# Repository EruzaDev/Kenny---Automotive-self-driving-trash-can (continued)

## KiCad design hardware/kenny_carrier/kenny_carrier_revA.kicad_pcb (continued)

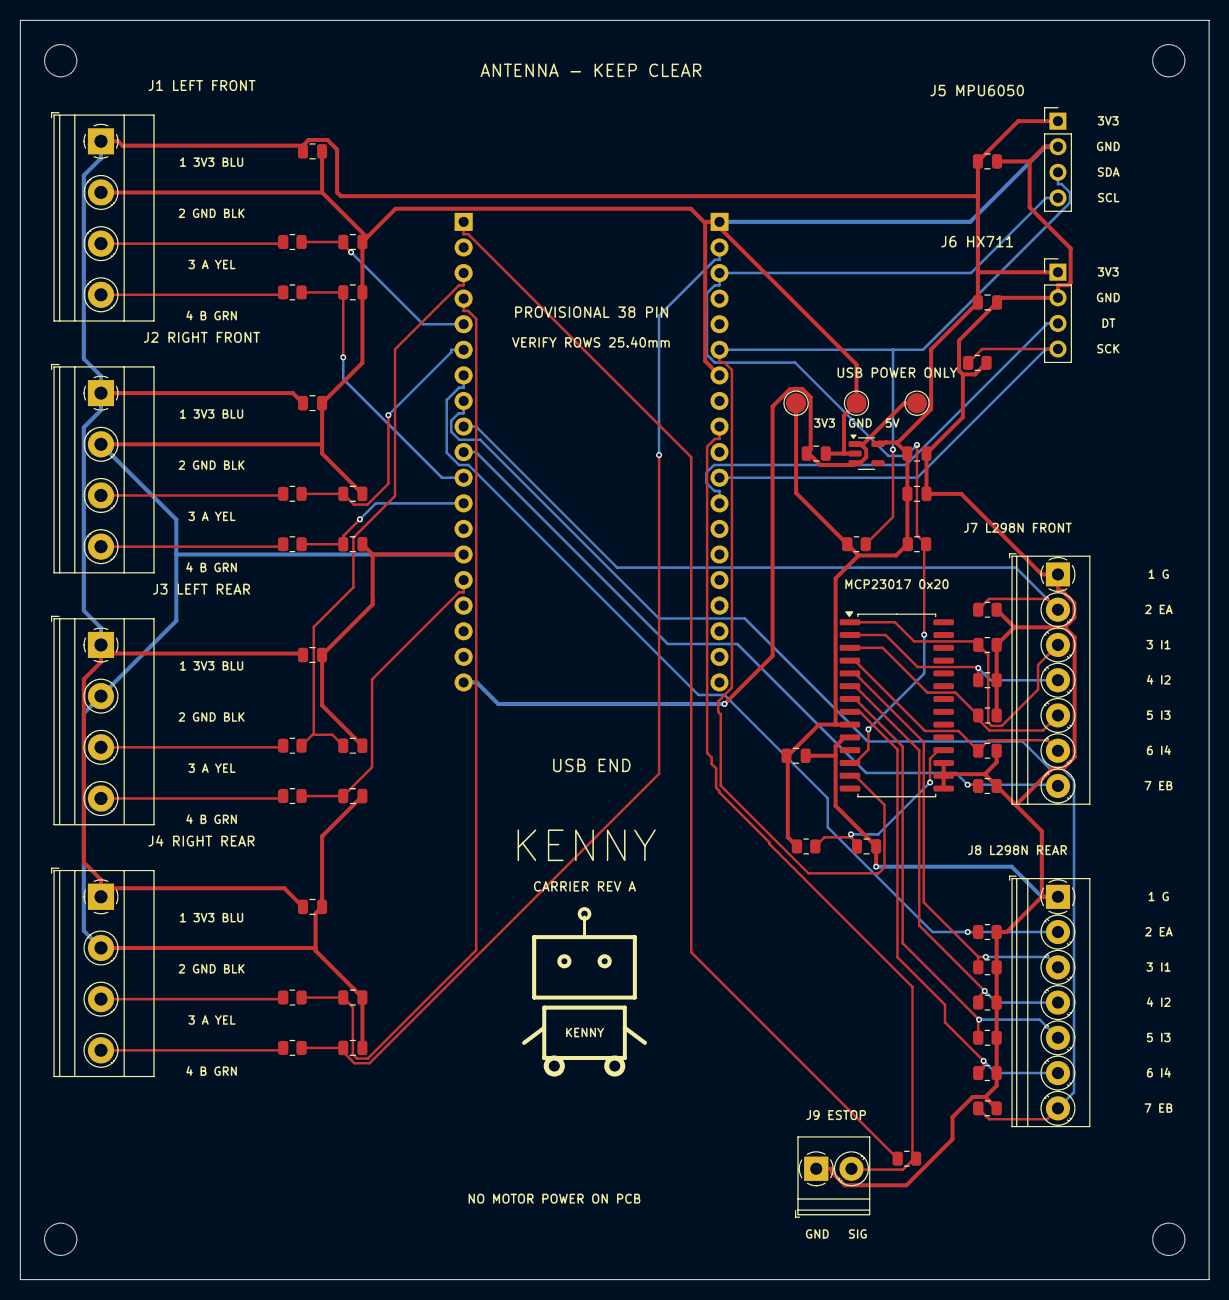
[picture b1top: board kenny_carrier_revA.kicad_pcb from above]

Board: 2 copper layers, 118.0 x 125.0 mm, 63 parts (0 on the bottom side), 38 nets.

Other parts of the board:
H1, H2, H3, H4: MountingHole_3.2mm_M3

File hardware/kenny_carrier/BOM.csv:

Reference,Value,Footprint,Description
U1,ESP32-WROOM 38pin PROVISIONAL,Kenny:ESP32_38_PROVISIONAL,2x19 female sockets; 2.54mm pitch; assumed 25.40mm row spacing; verify module
U2,MCP23017-E/SO,Package_SO:SOIC-28W_7.5x17.9mm_P1.27mm,"I2C address 0x20, GPB0..7 independent motor directions"
U3,AP2112K-3.3TRG1,Package_TO_SOT_SMD:SOT-23-5,Peripheral 3.3V LDO; input from DevKit USB 5V pin ONLY; 150mA initial budget
J1,LF ENCODER,"TerminalBlock_Phoenix:TerminalBlock_Phoenix_MKDS-1,5-4-5.08_1x04_P5.08mm_Horizontal","5.08mm 4-way terminal; 1 BLUE +3V3, 2 BLACK GND, 3 YELLOW A, 4 GREEN B"
R1,1k,Resistor_SMD:R_0805_2012Metric,"Encoder series resistor, together with 1nF gives 1us RC; NOT a level shifter"
C1,1nF 50V C0G,Capacitor_SMD:C_0805_2012Metric,
R2,1k,Resistor_SMD:R_0805_2012Metric,"Encoder series resistor, together with 1nF gives 1us RC; NOT a level shifter"
C2,1nF 50V C0G,Capacitor_SMD:C_0805_2012Metric,
C9,100nF 16V X7R,Capacitor_SMD:C_0805_2012Metric,
J2,RF ENCODER,"TerminalBlock_Phoenix:TerminalBlock_Phoenix_MKDS-1,5-4-5.08_1x04_P5.08mm_Horizontal","5.08mm 4-way terminal; 1 BLUE +3V3, 2 BLACK GND, 3 YELLOW A, 4 GREEN B"
R3,1k,Resistor_SMD:R_0805_2012Metric,"Encoder series resistor, together with 1nF gives 1us RC; NOT a level shifter"
C3,1nF 50V C0G,Capacitor_SMD:C_0805_2012Metric,
R4,1k,Resistor_SMD:R_0805_2012Metric,"Encoder series resistor, together with 1nF gives 1us RC; NOT a level shifter"
C4,1nF 50V C0G,Capacitor_SMD:C_0805_2012Metric,
C10,100nF 16V X7R,Capacitor_SMD:C_0805_2012Metric,
J3,LR ENCODER,"TerminalBlock_Phoenix:TerminalBlock_Phoenix_MKDS-1,5-4-5.08_1x04_P5.08mm_Horizontal","5.08mm 4-way terminal; 1 BLUE +3V3, 2 BLACK GND, 3 YELLOW A, 4 GREEN B"
R5,1k,Resistor_SMD:R_0805_2012Metric,"Encoder series resistor, together with 1nF gives 1us RC; NOT a level shifter"
C5,1nF 50V C0G,Capacitor_SMD:C_0805_2012Metric,
R6,1k,Resistor_SMD:R_0805_2012Metric,"Encoder series resistor, together with 1nF gives 1us RC; NOT a level shifter"
C6,1nF 50V C0G,Capacitor_SMD:C_0805_2012Metric,
C11,100nF 16V X7R,Capacitor_SMD:C_0805_2012Metric,
J4,RR ENCODER,"TerminalBlock_Phoenix:TerminalBlock_Phoenix_MKDS-1,5-4-5.08_1x04_P5.08mm_Horizontal","5.08mm 4-way terminal; 1 BLUE +3V3, 2 BLACK GND, 3 YELLOW A, 4 GREEN B"
R7,1k,Resistor_SMD:R_0805_2012Metric,"Encoder series resistor, together with 1nF gives 1us RC; NOT a level shifter"
C7,1nF 50V C0G,Capacitor_SMD:C_0805_2012Metric,
R8,1k,Resistor_SMD:R_0805_2012Metric,"Encoder series resistor, together with 1nF gives 1us RC; NOT a level shifter"
C8,1nF 50V C0G,Capacitor_SMD:C_0805_2012Metric,
C12,100nF 16V X7R,Capacitor_SMD:C_0805_2012Metric,
J5,MPU6050,Connector_PinHeader_2.54mm:PinHeader_1x04_P2.54mm_Vertical,"2.54mm Dupont: 3V3 GND SDA SCL; wire by signal, module header order can differ"
J6,HX711 MODULE,Connector_PinHeader_2.54mm:PinHeader_1x04_P2.54mm_Vertical,2.54mm Dupont: 3V3 GND DT SCK; raw load cell goes to HX711 E+/E-/A+/A-
J7,L298N FRONT,"TerminalBlock_Phoenix:TerminalBlock_Phoenix_PT-1,5-7-3.5-H_1x07_P3.50mm_Horizontal",3.50mm 7-way terminal: GND ENA IN1 IN2 IN3 IN4 ENB; logic only
J8,L298N REAR,"TerminalBlock_Phoenix:TerminalBlock_Phoenix_PT-1,5-7-3.5-H_1x07_P3.50mm_Horizontal",3.50mm 7-way terminal: GND ENA IN1 IN2 IN3 IN4 ENB; logic only
J9,ESTOP NC,"TerminalBlock_Phoenix:TerminalBlock_Phoenix_PT-1,5-2-3.5-H_1x02_P3.50mm_Horizontal",3.50mm 2-way terminal; normally-closed contact to GND; open=stop; external power cut remains required
R9,10k,Resistor_SMD:R_0805_2012Metric,Direction pull-down; MCP pins are high impedance during reset
R10,10k,Resistor_SMD:R_0805_2012Metric,Direction pull-down; MCP pins are high impedance during reset
R11,10k,Resistor_SMD:R_0805_2012Metric,Direction pull-down; MCP pins are high impedance during reset
R12,10k,Resistor_SMD:R_0805_2012Metric,Direction pull-down; MCP pins are high impedance during reset
R13,10k,Resistor_SMD:R_0805_2012Metric,Direction pull-down; MCP pins are high impedance during reset
R14,10k,Resistor_SMD:R_0805_2012Metric,Direction pull-down; MCP pins are high impedance during reset
R15,10k,Resistor_SMD:R_0805_2012Metric,Direction pull-down; MCP pins are high impedance during reset
R16,10k,Resistor_SMD:R_0805_2012Metric,Direction pull-down; MCP pins are high impedance during reset
R17,10k,Resistor_SMD:R_0805_2012Metric,Enable pull-down; REMOVE L298N ENA/ENB jumpers
R18,10k,Resistor_SMD:R_0805_2012Metric,Enable pull-down; REMOVE L298N ENA/ENB jumpers
R19,10k,Resistor_SMD:R_0805_2012Metric,Enable pull-down; REMOVE L298N ENA/ENB jumpers
R20,10k,Resistor_SMD:R_0805_2012Metric,Enable pull-down; REMOVE L298N ENA/ENB jumpers
R21,4.7k,Resistor_SMD:R_0805_2012Metric,I2C pull-up; depopulate if module pull-ups make total too low
R22,4.7k,Resistor_SMD:R_0805_2012Metric,I2C pull-up
R23,10k,Resistor_SMD:R_0805_2012Metric,MCP reset pull-up
R24,10k,Resistor_SMD:R_0805_2012Metric,E-stop input pull-up
R25,10k,Resistor_SMD:R_0805_2012Metric,Hold HX711 clock low during ESP reset
C13,1uF 16V X7R,Capacitor_SMD:C_0805_2012Metric,
C14,10uF 10V X5R,Capacitor_SMD:C_0805_2012Metric,
C15,100nF 16V X7R,Capacitor_SMD:C_0805_2012Metric,
C16,100nF 16V X7R,Capacitor_SMD:C_0805_2012Metric,
C17,100nF 16V X7R,Capacitor_SMD:C_0805_2012Metric,
C18,10uF 10V X5R,Capacitor_SMD:C_0805_2012Metric,
C19,100nF 16V X7R,Capacitor_SMD:C_0805_2012Metric,
TP1,+3V3,TestPoint:TestPoint_Pad_D2.0mm,Supply measurement
TP2,GND,TestPoint:TestPoint_Pad_D2.0mm,Supply measurement
TP3,USB_5V,TestPoint:TestPoint_Pad_D2.0mm,Supply measurement

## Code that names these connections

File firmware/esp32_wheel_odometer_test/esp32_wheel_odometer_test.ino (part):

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 *   - Four JGB37-520 encoder gearmotors with 80 mm wheels (r = 0.04 m)
 *
 * Control Wiring (same on both Left and Right ESP32):
 *   Motor 1 (OUT1/OUT2): ENA = GPIO32, IN1 = GPIO23, IN2 = GPIO13
 *   Motor 2 (OUT3/OUT4): ENB = GPIO27, IN3 = GPIO19, IN4 = GPIO4
 *
 * Encoder Wiring (docs/ESP32_MOTOR_WIRING.md):
 *   LEFT ESP32 (M1 left rear, M2 left front):
 *     Motor 1: A = GPIO34, B = GPIO25
 *     Motor 2: A = GPIO18, B = GPIO21
 *   RIGHT ESP32:
 *     Motor 1: A = GPIO34, B = GPIO25
 *     Motor 2: A = GPIO18, B = GPIO21
 *   Note: GPIO34 is an input-only pin on ESP32 and has NO internal pull-up.
 *
 * Serial Protocol (115200 baud, \n line endings):
 *   Commands:
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// ============================================================================
static int pinInputMode(int gpio_pin) {
  if (gpio_pin >= 34) {
    return INPUT;  // GPIO34..39 are input-only and lack internal pull-ups
  }
  return use_internal_pullups ? INPUT_PULLUP : INPUT;
}
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    if (arg && strcasecmp(arg, "ON") == 0) {
      use_internal_pullups = true;
      configureEncoderPins(is_left_side);
      Serial.println(F("# OK PULLUP ON (GPIO34 remains external-only)"));
    } else if (arg && strcasecmp(arg, "OFF") == 0) {
      use_internal_pullups = false;
      configureEncoderPins(is_left_side);
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
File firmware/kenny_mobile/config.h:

#pragma once
#include <cstdint>

#define KENNY_DIRECT_GPIO 1
#define KENNY_CARRIER_MCP23017 2

// IMPORTANT: select the wiring actually installed before uploading.
// 1 = the earlier independent-GPIO L298N wiring.
// 2 = hardware/kenny_carrier PCB (MCP23017 directions, E-stop GPIO18).
#ifndef KENNY_WIRING
#define KENNY_WIRING KENNY_DIRECT_GPIO
#endif
#if KENNY_WIRING != KENNY_DIRECT_GPIO && KENNY_WIRING != KENNY_CARRIER_MCP23017
#error "Select KENNY_DIRECT_GPIO or KENNY_CARRIER_MCP23017"
#endif

constexpr char WIFI_SSID[] = "KENNY-Robot";
constexpr char WIFI_PASSWORD[] = "KennyDrive!2026";  // Default local Wi-Fi password.
static_assert(sizeof(WIFI_PASSWORD) >= 9, "Wi-Fi password must have at least 8 characters");
constexpr uint32_t ENCODER_CPR = 1320;  // Expected x4 count; replace with measured CPR.
constexpr float WHEEL_RADIUS = 0.040f;
constexpr float NOMINAL_RPM = 333.0f;
constexpr int MAX_PWM = 90;
constexpr float KP = 1.5f, KI = 0.5f;  // Commissioning gains; tune on raised wheels.
constexpr float RPM_SLEW_PER_SECOND = 40.0f;
constexpr uint32_t ENCODER_TIMEOUT_MS = 500;
constexpr unsigned MOTOR_COUNT = 4;

#if KENNY_WIRING == KENNY_CARRIER_MCP23017
constexpr uint8_t ESTOP_PIN = 18;
constexpr uint8_t I2C_SDA = 21, I2C_SCL = 22, MCP_ADDRESS = 0x20;
constexpr uint8_t HX_DOUT = 16, HX_SCK = 17;
constexpr char WIRING_NAME[] = "Carrier PCB / MCP23017";
#else
constexpr uint8_t ESTOP_PIN = 15;
constexpr char WIRING_NAME[] = "Direct GPIO";
#endif
